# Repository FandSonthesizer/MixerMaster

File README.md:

# MixerMaster
This is the master pcb for the modular mixer.
All Channel strips daisy-chain and the master sits at the end of that chain.

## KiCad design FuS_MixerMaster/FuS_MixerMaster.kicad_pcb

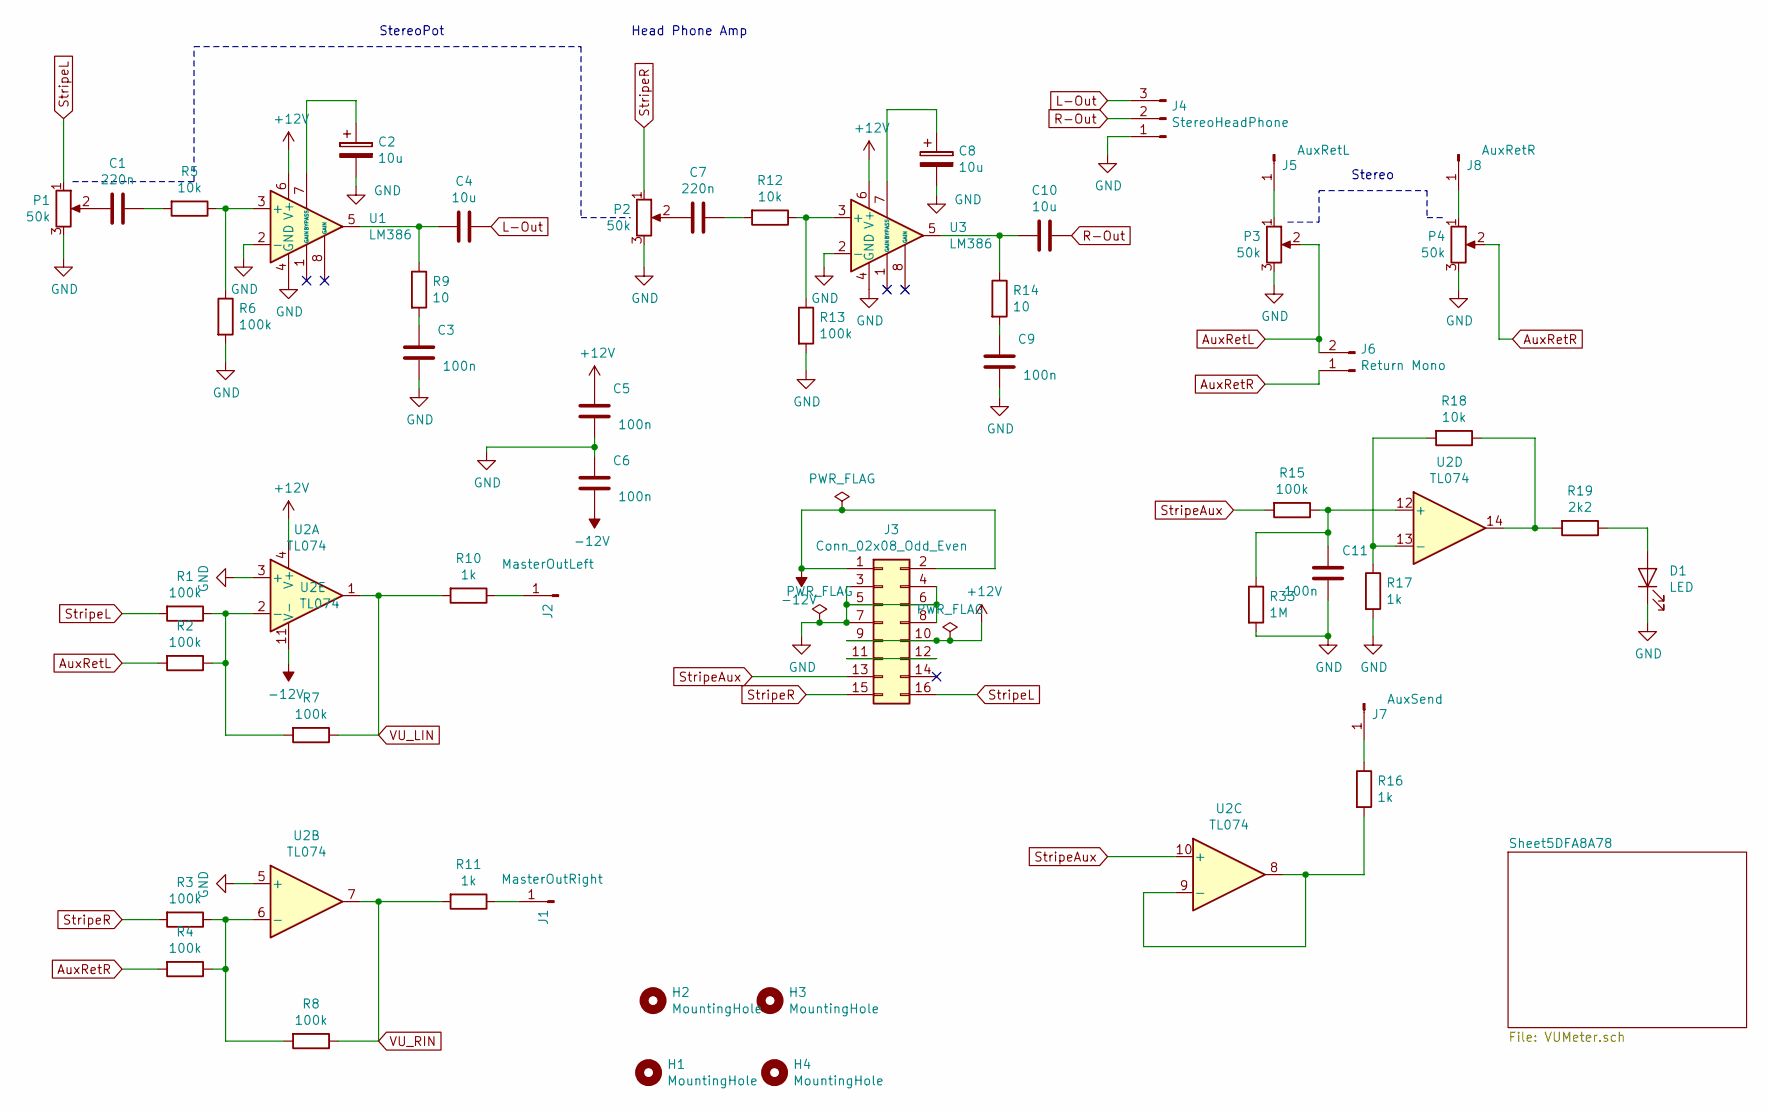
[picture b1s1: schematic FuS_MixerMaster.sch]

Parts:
C1, C7: 220n; Kondensator_Keramik
C2, C8: 10u; Elko_D6.3mm_P2.50mm
C3, C5, C6, C9, C11: 100n; Kondensator_Keramik
C4, C10: 10u; Kondensator_Keramik
D1: LED; Diode_Horizontal
H1, H2, H3, H4: MountingHole; MountHole
J1: MasterOutRight; Stift
J2: MasterOutLeft; Stift
J3: Conn_02x08_Odd_Even; PinHeader_2x08_P2.54mm_Vertical
J4: StereoHeadPhone; Stift_0x3
J5: AuxRetL; Stift
J6: Return Mono; Stift_x02
J7: AuxSend; Stift
J8: AuxRetR; Stift
P1, P2, P3, P4: 50k; Trimmer_Vertical
R1, R2, R3, R4, R6, R7, R8, R13, R15: 100k; Widerstand_liegend
R5, R12, R18: 10k; Widerstand_liegend
R9, R14: 10; Widerstand_liegend
R10, R11, R16, R17: 1k; Widerstand_liegend
R19: 2k2; Widerstand_liegend
R33: 1M; Widerstand_liegend
U1, U3: LM386; DIP-8_W7.62mm_LongPads
U2: TL074; DIP-14_W7.62mm_Socket_LongPads

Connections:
+12V: C5.2, J3.9, J3.10, U1.6 (V+), U2.4 (V+), U3.6 (V+); also elsewhere on the board
-12V: C6.1, J3.1, J3.2, U2.11 (V-); also elsewhere on the board
AuxRetL: J6.2, P3.2, R2.2
AuxRetR: J6.1, P4.2, R4.2
GND: C2.2, C3.1, C5.1, C6.2, C8.2, C9.1, C11.1, D1.1 (K), J3.3, J3.4, J3.5, J3.6, J3.7, J3.8, J4.1, P1.3, P2.3, P3.3, P4.3, R6.2, R13.2, R17.2, R33.2, U1.2 (-), U1.4 (GND), U2.3 (+), U2.5 (+), U3.2 (-), U3.4 (GND); also elsewhere on the board
L-Out: C4.1, J4.3
unnamed: C1.1, R5.2
unnamed: C1.2, P1.2
unnamed: C2.1, U1.7 (BYPASS)
unnamed: C3.2, R9.2
unnamed: C4.2, R9.1, U1.5
unnamed: C7.1, R12.2
unnamed: C7.2, P2.2
unnamed: C8.1, U3.7 (BYPASS)
unnamed: C9.2, R14.2
unnamed: C10.2, R14.1, U3.5
unnamed: C11.2, R15.1, R33.1, U2.12 (+)
unnamed: D1.2 (A), R19.1
unnamed: J1.1, R11.1
unnamed: J2.1, R10.1
unnamed: J3.11, J3.12
unnamed: J5.1, P3.1
unnamed: J7.1, R16.1
unnamed: J8.1, P4.1
unnamed: R1.1, R2.1, R7.2, U2.2 (-)
unnamed: R3.1, R4.1, R8.2, U2.6 (-)
unnamed: R5.1, R6.1, U1.3 (+)
unnamed: R12.1, R13.1, U3.3 (+)
unnamed: R16.2, U2.8, U2.9 (-)
unnamed: R17.1, R18.2, U2.13 (-)
unnamed: R18.1, R19.2, U2.14
R-Out: C10.1, J4.2
StripeAux: J3.13, R15.2, U2.10 (+)
StripeL: J3.16, P1.1, R1.2
StripeR: J3.15, P2.1, R3.2
VU_LIN: R7.1, R10.2, U2.1; also elsewhere on the board
VU_RIN: R8.1, R11.2, U2.7; also elsewhere on the board

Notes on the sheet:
StereoPot
Head Phone Amp
Stereo

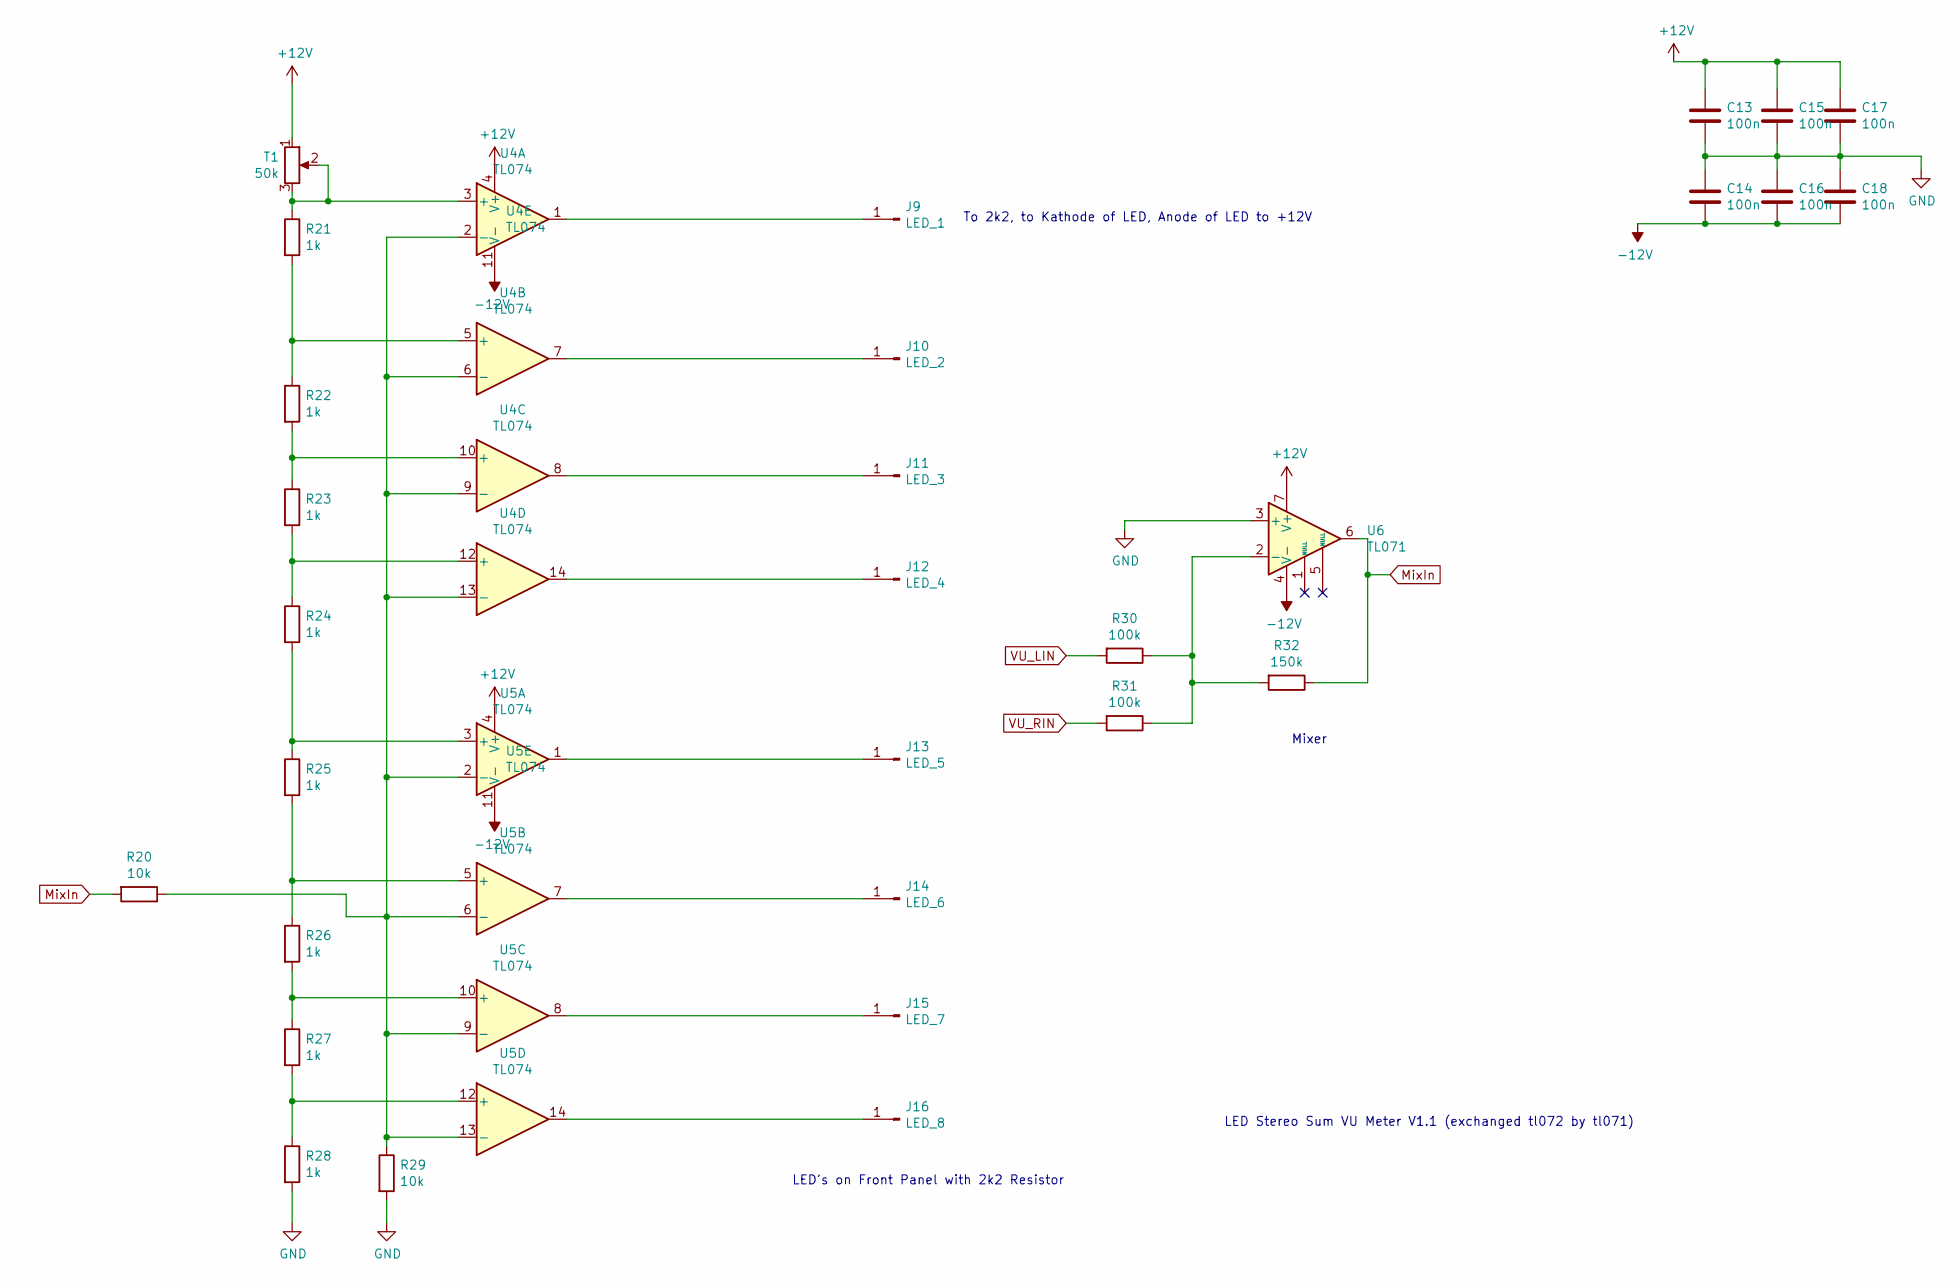
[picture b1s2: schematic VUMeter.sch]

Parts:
C13, C14, C15, C16, C17, C18: 100n; Kondensator_Keramik
J9: LED_1; Stift
J10: LED_2; Stift
J11: LED_3; Stift
J12: LED_4; Stift
J13: LED_5; Stift
J14: LED_6; Stift
J15: LED_7; Stift
J16: LED_8; Stift
R20, R29: 10k; Widerstand_liegend
R21, R22, R23, R24, R25, R26, R27, R28: 1k; Widerstand_liegend
R30, R31: 100k; Widerstand_liegend
R32: 150k; Widerstand_liegend
T1: 50k; Trimmer_Vertical
U4, U5: TL074; DIP-14_W7.62mm_Socket_LongPads
U6: TL071; DIP-8_W7.62mm_LongPads

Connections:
+12V: C13.1, C15.1, C17.1, T1.1, U4.4 (V+), U5.4 (V+), U6.7 (V+); also elsewhere on the board
-12V: C14.2, C16.2, C18.2, U4.11 (V-), U5.11 (V-), U6.4 (V-); also elsewhere on the board
GND: C13.2, C14.1, C15.2, C16.1, C17.2, C18.1, R28.2, R29.2, U6.3 (+); also elsewhere on the board
MixIn: R20.2, R32.1, U6.6
unnamed: J9.1, U4.1
unnamed: J10.1, U4.7
unnamed: J11.1, U4.8
unnamed: J12.1, U4.14
unnamed: J13.1, U5.1
unnamed: J14.1, U5.7
unnamed: J15.1, U5.8
unnamed: J16.1, U5.14
unnamed: R20.1, R29.1, U4.2 (-), U4.6 (-), U4.9 (-), U4.13 (-), U5.2 (-), U5.6 (-), U5.9 (-), U5.13 (-)
unnamed: R21.1, T1.2, T1.3, U4.3 (+)
unnamed: R21.2, R22.1, U4.5 (+)
unnamed: R22.2, R23.1, U4.10 (+)
unnamed: R23.2, R24.1, U4.12 (+)
unnamed: R24.2, R25.1, U5.3 (+)
unnamed: R25.2, R26.1, U5.5 (+)
unnamed: R26.2, R27.1, U5.10 (+)
unnamed: R27.2, R28.1, U5.12 (+)
unnamed: R30.1, R31.1, R32.2, U6.2 (-)
VU_LIN: R30.2; also elsewhere on the board
VU_RIN: R31.2; also elsewhere on the board

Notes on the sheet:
Mixer
LED Stereo Sum VU Meter V1.1 (exchanged tl072 by tl071)
LED's on Front Panel with 2k2 Resistor
To 2k2, to Kathode of LED, Anode of LED to +12V

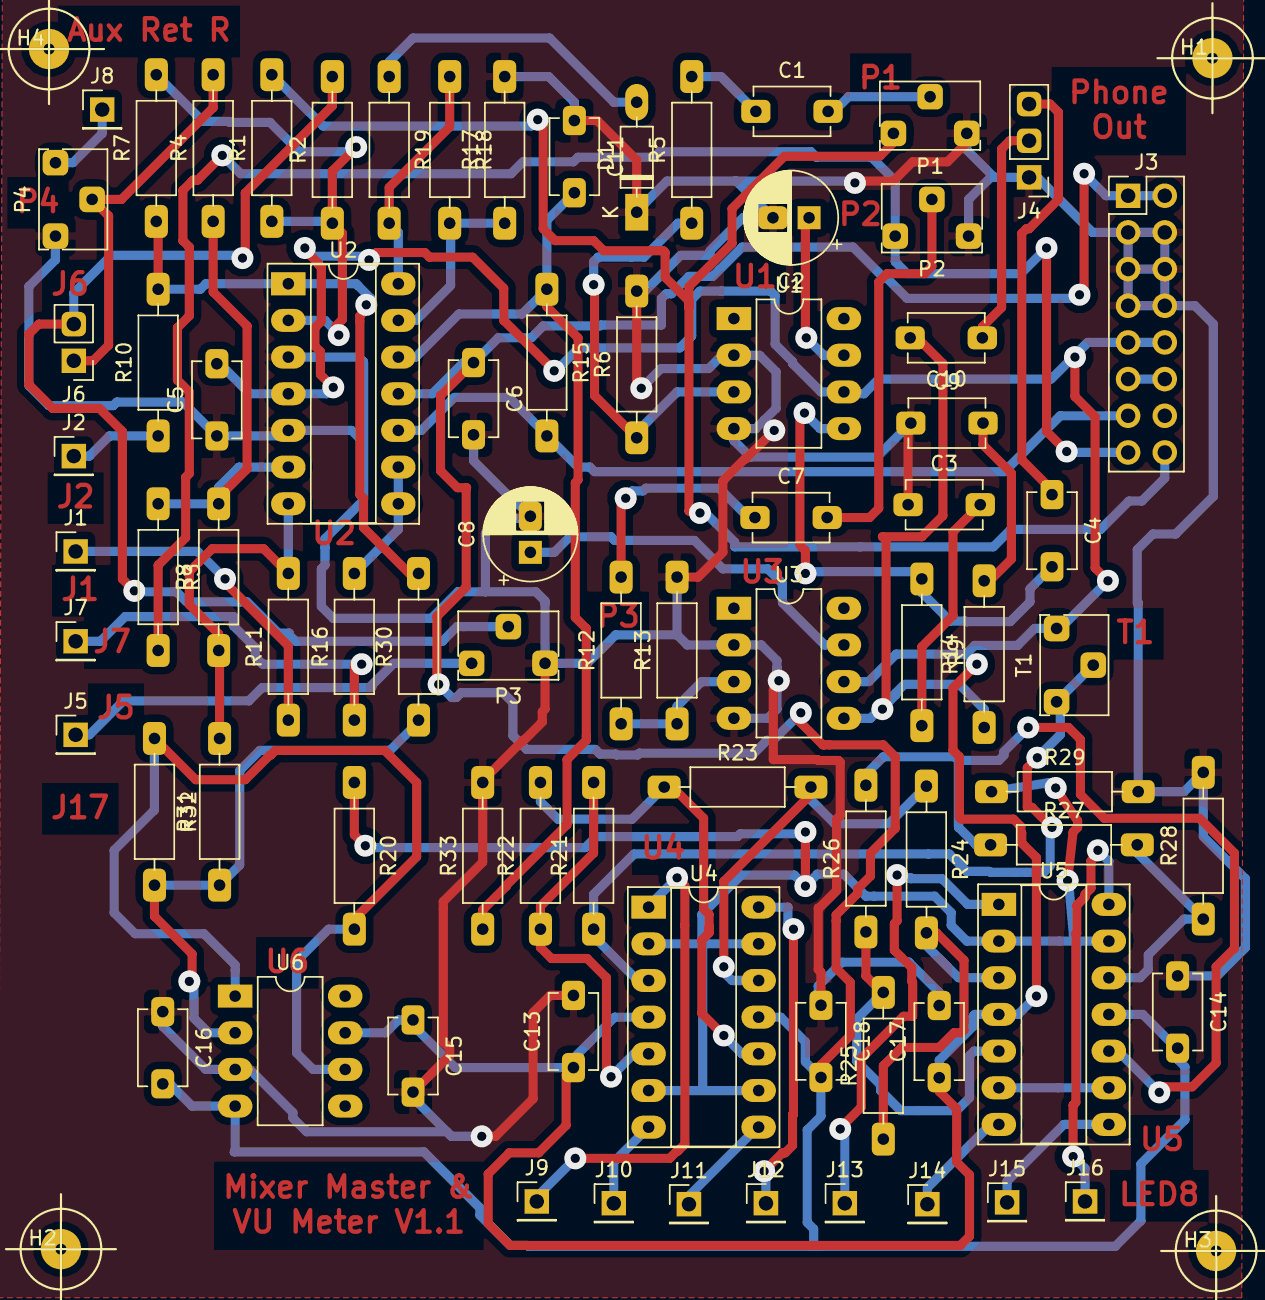
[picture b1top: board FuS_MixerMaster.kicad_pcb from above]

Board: 2 copper layers, 82 parts (0 on the bottom side), 56 nets.

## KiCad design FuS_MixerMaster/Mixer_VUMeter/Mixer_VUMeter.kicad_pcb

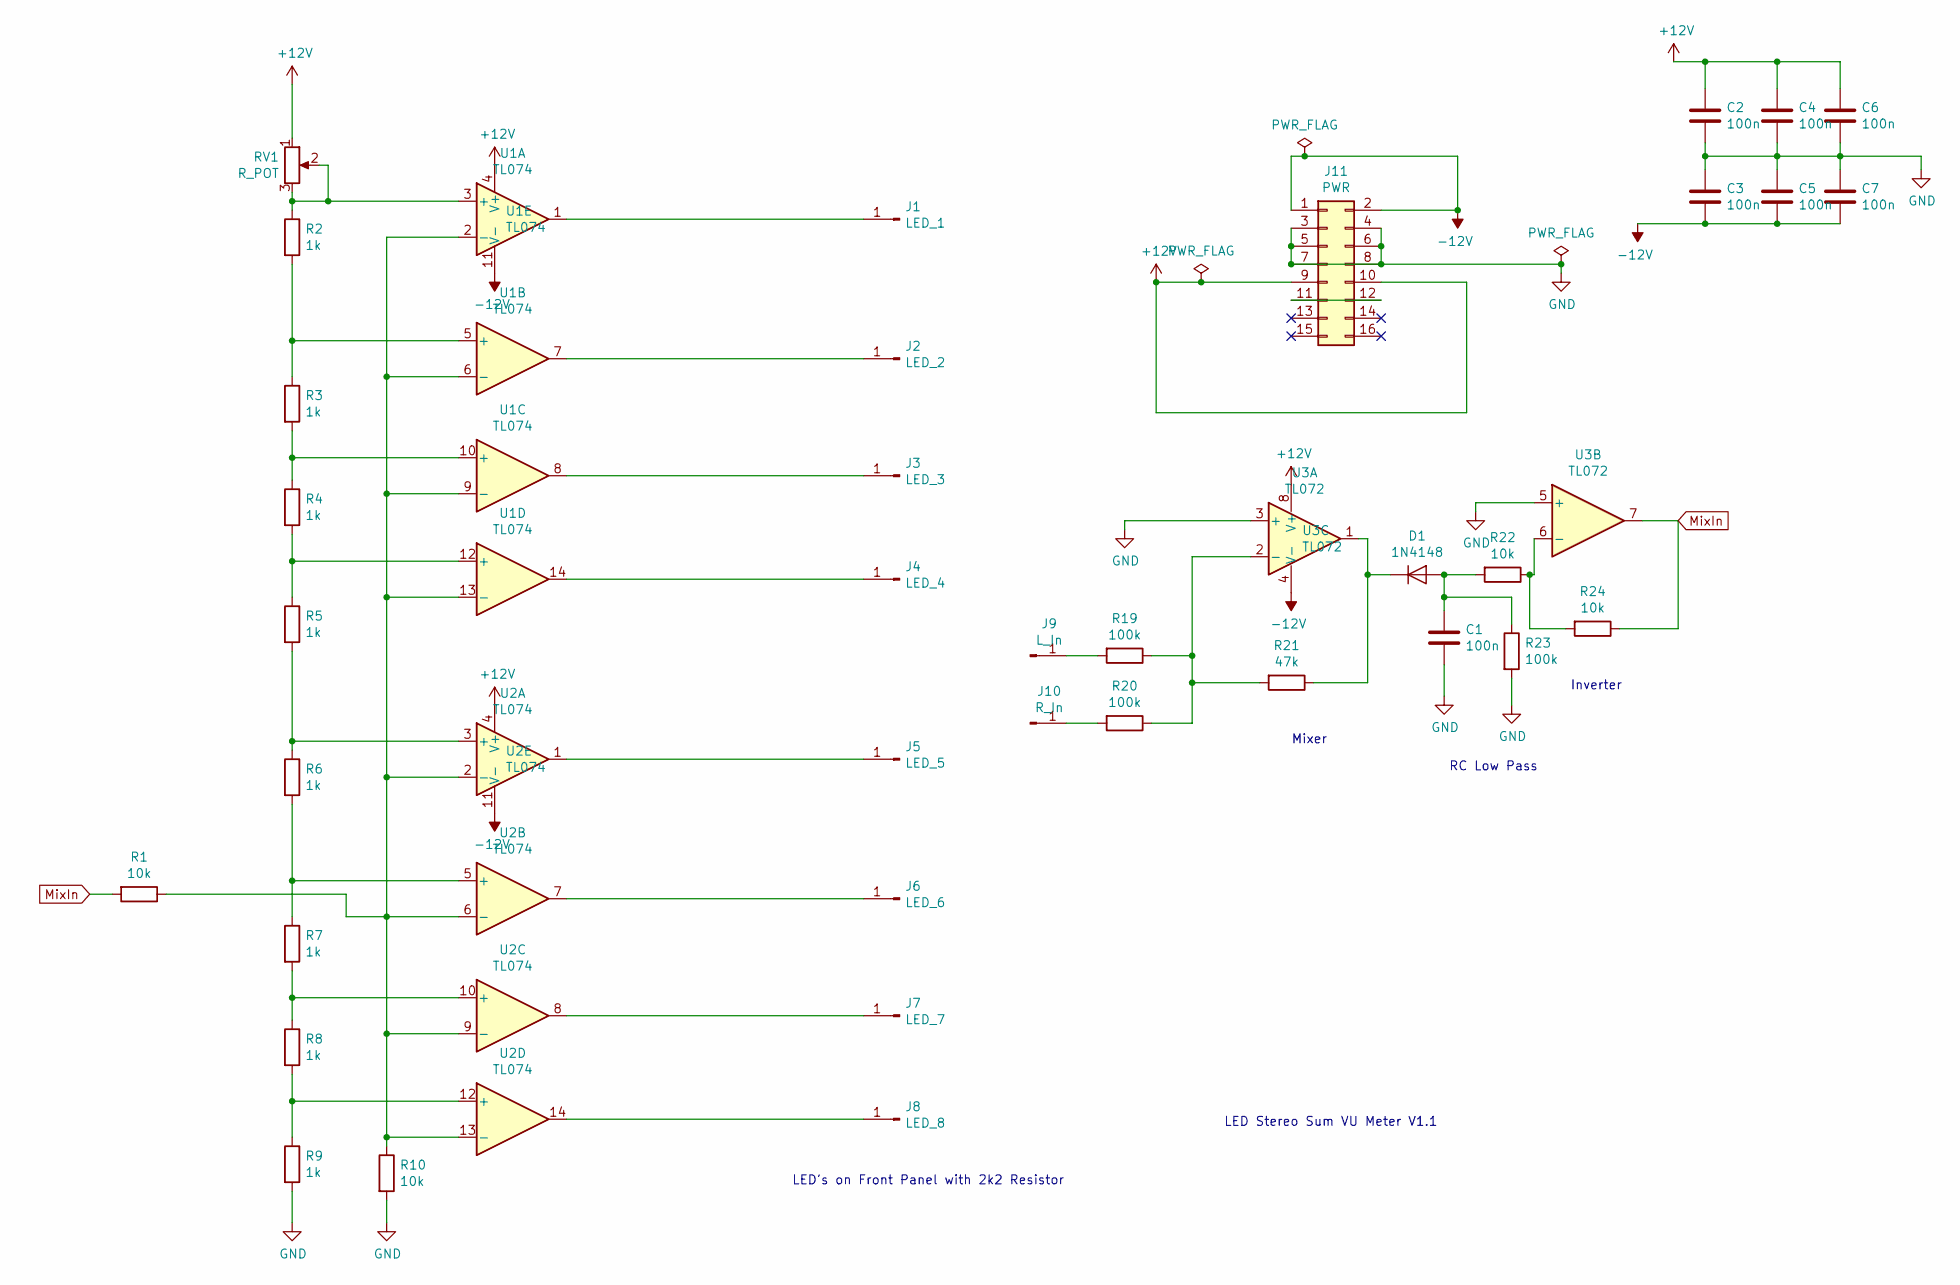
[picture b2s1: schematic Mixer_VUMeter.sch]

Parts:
C1, C2, C3, C4, C5, C6, C7: 100n; Kondensator_Keramik
D1: 1N4148; Diode_Horizontal
J1: LED_1; Stift
J2: LED_2; Stift
J3: LED_3; Stift
J4: LED_4; Stift
J5: LED_5; Stift
J6: LED_6; Stift
J7: LED_7; Stift
J8: LED_8; Stift
J9: L_In; Stift
J10: R_In; Stift
J11: PWR; PinHeader_2x08_P2.54mm_Vertical
R1, R10, R22, R24: 10k; Widerstand_liegend
R2, R3, R4, R5, R6, R7, R8, R9: 1k; Widerstand_liegend
R19, R20, R23: 100k; Widerstand_liegend
R21: 47k; Widerstand_liegend
RV1: R_POT; Trimmer_Vertical
U1, U2: TL074; DIP-14_W7.62mm_Socket_LongPads
U3: TL072; DIP-8_W7.62mm_Socket_LongPads

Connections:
+12V: C2.1, C4.1, C6.1, J11.9, J11.10, RV1.1, U1.4 (V+), U2.4 (V+), U3.8 (V+)
-12V: C3.2, C5.2, C7.2, J11.1, J11.2, U1.11 (V-), U2.11 (V-), U3.4 (V-)
GND: C1.2, C2.2, C3.1, C4.2, C5.1, C6.2, C7.1, J11.3, J11.4, J11.5, J11.6, J11.7, J11.8, R9.2, R10.2, R23.2, U3.3 (+), U3.5 (+)
MixIn: R1.2, R24.1, U3.7
unnamed: C1.1, D1.2 (A), R22.2, R23.1
unnamed: D1.1 (K), R21.1, U3.1
unnamed: J1.1, U1.1
unnamed: J2.1, U1.7
unnamed: J3.1, U1.8
unnamed: J4.1, U1.14
unnamed: J5.1, U2.1
unnamed: J6.1, U2.7
unnamed: J7.1, U2.8
unnamed: J8.1, U2.14
unnamed: J9.1, R19.2
unnamed: J10.1, R20.2
unnamed: J11.11, J11.12
unnamed: R1.1, R10.1, U1.2 (-), U1.6 (-), U1.9 (-), U1.13 (-), U2.2 (-), U2.6 (-), U2.9 (-), U2.13 (-)
unnamed: R2.1, RV1.2, RV1.3, U1.3 (+)
unnamed: R2.2, R3.1, U1.5 (+)
unnamed: R3.2, R4.1, U1.10 (+)
unnamed: R4.2, R5.1, U1.12 (+)
unnamed: R5.2, R6.1, U2.3 (+)
unnamed: R6.2, R7.1, U2.5 (+)
unnamed: R7.2, R8.1, U2.10 (+)
unnamed: R8.2, R9.1, U2.12 (+)
unnamed: R19.1, R20.1, R21.2, U3.2 (-)
unnamed: R22.1, R24.2, U3.6 (-)

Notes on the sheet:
Mixer
Inverter
LED Stereo Sum VU Meter V1.1
RC Low Pass
LED's on Front Panel with 2k2 Resistor

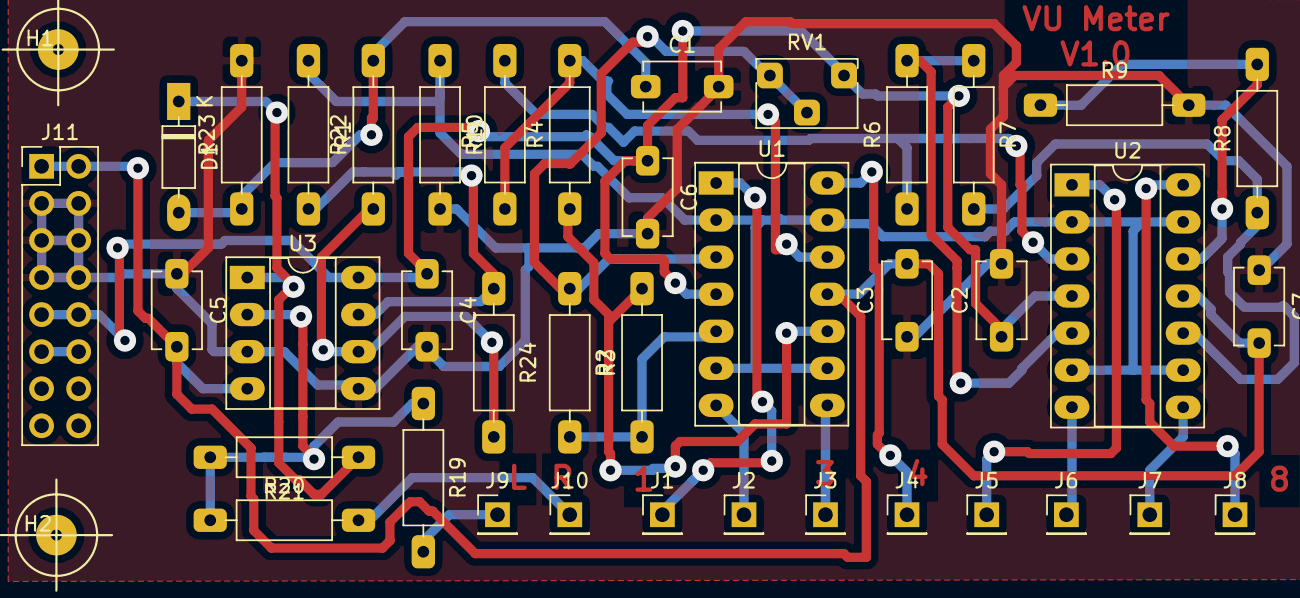
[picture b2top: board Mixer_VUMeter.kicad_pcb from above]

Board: 2 copper layers, 41 parts (0 on the bottom side), 28 nets.

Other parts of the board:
H1, H2: MountingHole; MountHole
